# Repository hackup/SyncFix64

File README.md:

# SyncFix64

LM1881 based quick-fix for the C64 VSync. See [hackup.net](https://www.hackup.net/tag/syncfix64/) for details.

## License

To avoid further confusion, proper licensing of this project has now been added. If you are interested in obtaining a different license, please get in contact.

This work is licensed under a [Creative Commons Attribution-NonCommercial-ShareAlike 4.0 International License](http://creativecommons.org/licenses/by-nc-sa/4.0/).

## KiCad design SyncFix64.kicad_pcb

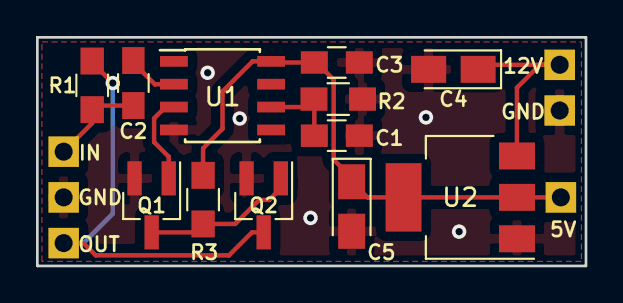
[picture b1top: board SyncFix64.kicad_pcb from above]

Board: 2 copper layers, 30.5 x 12.7 mm, 15 parts (0 on the bottom side), 9 nets.

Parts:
C1, C2, C3: 100n; C_0805_HandSoldering
C4, C5: CP; CP_Tantalum_Case-A_EIA-3216-18_Reflow
J1: Pwr; Pin_Header_Straight_1x02_Pitch2.54mm
J2: Video; Pin_Header_Straight_1x03_Pitch2.54mm
J3: AltPwr; Pin_Header_Straight_1x01_Pitch2.54mm
Q1, Q2: BSS138; SOT-23_Handsoldering
R1: 100; R_0805_HandSoldering
R2: 680k; R_0805_HandSoldering
R3: 10k; R_0805_HandSoldering
U1: LM1881; SOIC-8_3.9x4.9mm_Pitch1.27mm
U2: AMS1117-50; SOT-223-3_TabPin2

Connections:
+5V: C3.2, C5.1, J3.1, R3.1, U1.8, U2.2
+12V: C4.1, J1.1, U2.3
GND: C1.2, C3.1, C4.2, C5.2, J1.2, J2.2, Q1.2, Q2.2, R2.2, U1.4, U2.1
unnamed: C1.1, R2.1, U1.6
unnamed: C2.2, U1.2
unnamed: Q1.1, U1.3
unnamed: Q1.3, Q2.1, R3.2
VideoIN: C2.1, J2.3, R1.1
VideoOUT: J2.1, Q2.3, R1.2

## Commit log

2017-12-29 Initial commit.
2017-12-29 Minor fixes.
2017-12-31 Layout improvements.
2018-01-01 Updates for version 1.1.
2018-01-02 Added gerber dir.
2018-01-02 First Gerber export.
2018-05-28 Added logo.
2018-05-28 Clean up.
2018-05-28 Version increment.
2019-07-28 Added project license.
